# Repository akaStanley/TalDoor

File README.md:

# TalDoor (GatekeeperV2)
Spencer Kulbacki ~ CSH 2017-18

TalDoor (or GatekeeperV2) is a small POE door lock system that runs off the PocketBeagle and uses PN532 NFC module to scan and authenticate user ID cards and open the door.

## Hardware:
- [PocketBeagle](https://github.com/beagleboard/pocketbeagle)
- Pn532 NFC Module
- Esimated 500mA consumption of entire device during idle operation. Peak of 800mA during read/write  door motor operations. EST less than 3 WATT max POE requirements.

### Internal Main Board contains:
- PocketBeagle
- POE module
- Ethernet to SPI module
- Door lock motor driver
- 3.3 to 5v step up for motor drive
	
### External Reader Board contains:
- PN532 NFC reader
- Red/Green LEDs & Beeper for notification

### Part List for the PCB
+/- some pin headers we already have
~30$ in components for one board (+PCB Cost)

~62 components specified in BOM (not counting extra male pin headers)

QTY|Value
----|------
1|Buzzer
9|0.1uF
2|18pF
3|10uF
1|10000pF
1|10uF
1|470uF
3|1uF
4|G_LED
4|R_LED
1|SI-52003-F_RJ45
1|Conn_01x02
2|Conn_01x06_Male
1|Ferrite_Bead
1|PocketBeagle
1|RK7002BM
1|BSS223PWH6327XTSA1
1|100kΩ
2|10kΩ
2|180Ω
1|2.2kΩ
4|49.9Ω
8|68Ω
1|150Ω
1|DRV8837
1|ENC28J60-I/SO
1|PN532
1|AG9703
1|NCP1117-3.3
1|25MHz

## Software:
- LibNFC 1.7.1

## Notes
- [Paul's Github notes](https://github.com/woo2/gatekeeper-v2/tree/master/notes)
- [BestCo door lock info,sorta](http://www.bestaccess.com/files/6014/6184/1926/WMseries_WEB.pdf)
- Setting up ethernet forwarding over USB for BeagleBone dev on a PC
	- Plugin the BeagleBone to a USB port on your computer
	- Install the drivers
	- In control panel -> Adapter settings, set the IP address of the USB adapter to 192.168.7.1
	- On the adapter that has the internet connection, enable connection sharing with the USB adapter connection
	- ssh into the BeagleBone (ssh 192.168.7.2)
	- Run command "route add default gw 192.168.7.1"
	- Edit /etc/resolv.conf and add the Google name server by adding the line "nameserver 8.8.8.8"
	
- Door locks are 5v motors that need ~70mA to turn a worm gear and "unlock" the turnkey.
- BeagleBoard uses 130mA nom (300mA peak)
- 4 Red 0603 LEDs use 80mA
- ENC28J60-I/SO uses 120mA nom (180mA peak)
- PN532 91mA nom (140mA peak)
- Esimated 500mA consumption of entire device during idle operation. Peak of 800mA during read/write  door motor operations. EST less than 3 WATT max POE requirements.

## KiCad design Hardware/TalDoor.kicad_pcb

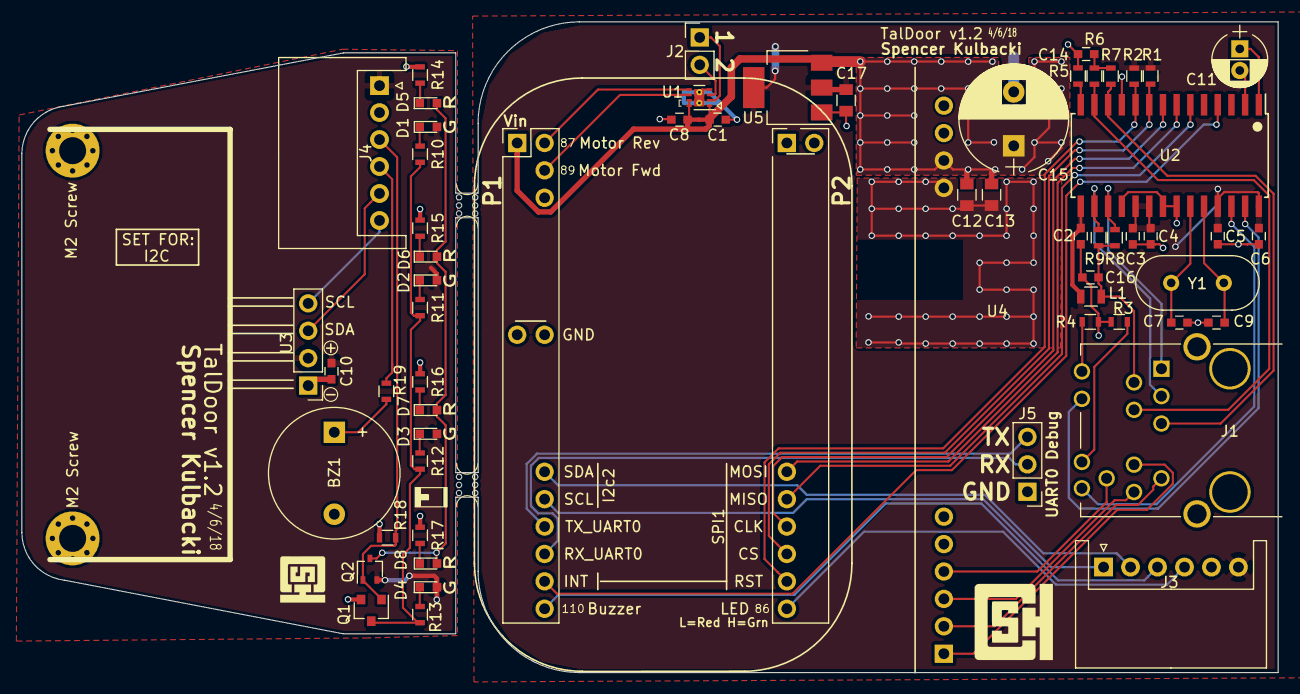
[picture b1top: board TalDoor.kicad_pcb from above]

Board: 2 copper layers, 116.5 x 60.3 mm, 64 parts (0 on the bottom side), 54 nets.

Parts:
BZ1: Buzzer; Buzzer_12x9.5RM7.6
C1, C2, C3, C4, C5, C6, C8, C10, C16: 0.1uF; C_0603
C7, C9: 18pF; C_0603
C11: 10uF; CP_Radial_D5.0mm_P2.00mm
C12, C13, C17: 10uF; C_0805
C14: 10000pF; C_0603
C15: 470uF; CP_Radial_D10.0mm_P5.00mm
D1, D2, D3, D4: G_LED; LED_0603
D5, D6, D7, D8: R_LED; LED_0603
J1: SI-52003-F_RJ45; RJ45_POE
J2: Conn_01x02; Pin_Header_Straight_1x02_Pitch2.54mm
J3, J4: Conn_01x06_Male; JST_XH_S06B-XH-A_06x2.50mm_Angled
J5: Conn_01x03; Pin_Header_Straight_1x03_Pitch2.54mm
L1: Ferrite_Bead; L_0805
M2 Screw, M2 Screw#2: MountingHole_2.2mm_M2_Pad_Via; MountingHole_2.5mm_Pad_Via
P1: PocketBeagle; PocketBeagle_TalDoor
Q1: RK7002BM; SOT-23
Q2: BSS223PWH6327XTSA1; SOT-323_SC-70
R1: 100k; R_0603
R2, R18: 10k; R_0603
R3, R4: 180; R_0603
R5: 2.2k; R_0603
R6, R7, R8, R9: 49.9; R_0603
R10, R11, R12, R13, R14, R15, R16, R17: 68; R_0603
R19: 120; R_0603
U1: DRV8837; WSON-8_1EP_2x2mm_Pitch0.5mm_ThermalVias
U2: ENC28J60-I/SO; SOIC-28W_7.5x17.9mm_Pitch1.27mm
U3: PN532
U4: AG9700; Ag9700_FP
U5: NCP1117-3.3_SOT223; SOT-223-3_TabPin2
Y1: 25MHz; Crystal_HC49-4H_Vertical
mouse-bite-2mm-slot, mouse-bite-2mm-slot#2: VAL**; mouse-bite-2mm-slot

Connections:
+3V3: C2.1, C3.1, C4.1, C5.1, C6.1, C17.1, J3.6, L1.2, R1.1, R2.1, U2.15, U2.19, U2.20, U2.25, U2.28, U5.2
+5V: C1.2, C8.2, C12.1, C13.1, C15.1, P1.1.1, U1.1, U1.7, U1.8, U4.8, U5.3
/+3.3v2: C10.2, D1.2, D2.2, D3.2, D4.2, J4.1, Q2.2, U3.2
/CLK: P1.2.29, U2.8
/CS: P1.2.31, R1.2, U2.9
/GND2: BZ1.2, C10.1, J4.2, Q1.2, R14.2, R15.2, R16.2, R17.2, R18.1, U3.1
/GPIO_86: J3.4, P1.2.35
/GPIO_87: P1.1.2, U1.5
/GPIO_89: P1.1.4, U1.6
/GPIO_110: J3.3, P1.1.36
/INT: P1.1.34, U2.4
/LEDA: J1.G+, U2.27
/LEDB: J1.Y+, U2.26
/MISO: P1.2.27, U2.6
/MOSI: P1.2.25, U2.7
/RST: P1.2.33, R2.2, U2.10
/RX_UART0: J5.2, P1.1.32
/SCL: J3.1, P1.1.28
/SDA: J3.2, P1.1.26
/TX_UART0: J5.3, P1.1.30
GND: C1.1, C2.2, C3.2, C4.2, C5.2, C6.2, C7.2, C8.1, C9.2, C11.2, C12.2, C13.2, C14.2, C15.2, C16.2, C17.2, J1.13, J3.5, J5.1, P1.1.15, P1.1.16, R3.1, R4.1, R5.1, U1.4, U2.2, U2.11, U2.18, U2.21, U2.22, U4.7, U5.1
unnamed: BZ1.1, R19.2
unnamed: C7.1, U2.23, Y1.2
unnamed: C9.1, U2.24, Y1.1
unnamed: C11.1, U2.1
unnamed: C14.1, R6.1, R7.1
unnamed: C16.1, J1.2, L1.1, R8.1, R9.1
unnamed: D1.1, R10.1
unnamed: D2.1, R11.1
unnamed: D3.1, R12.1
unnamed: D4.1, R13.1
unnamed: D5.1, R14.1
unnamed: D5.2, D6.2, D7.2, D8.2, Q2.3
unnamed: D6.1, R15.1
unnamed: D7.1, R16.1
unnamed: D8.1, R17.1
unnamed: J1.1, R8.2, U2.17
unnamed: J1.3, R9.2, U2.16
unnamed: J1.4, R6.2, U2.13
unnamed: J1.5, R7.2, U2.12
unnamed: J1.8, U4.1
unnamed: J1.9, U4.2
unnamed: J1.10, U4.3
unnamed: J1.11, U4.4
unnamed: J1.G-, R4.2
unnamed: J1.Y-, R3.2
unnamed: J2.1, U1.2
unnamed: J2.2, U1.3
unnamed: J4.3, Q1.1, Q2.1, R18.2
unnamed: J4.4, R19.1
unnamed: J4.5, U3.3
unnamed: J4.6, U3.4
unnamed: Q1.3, R10.2, R11.2, R12.2, R13.2
unnamed: R5.2, U2.14

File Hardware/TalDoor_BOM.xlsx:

TalDoor PCB
Generated: 4/8/2018 11:51:53 AM | 59
Component Count: | 59
Ref | QTY | Value | Footprint | Description | Digikey Part # | Per Unit | Cost | Notes
BZ1, | 1 | Buzzer | Buzzers_Beepers:Buzzer_12x9.5RM7.6 | Buzzer, polar | 668-1456-ND | 1.375 | 1.375
C2, C3, C4, C5, C6, C16, C1, C8, C10, | 9 | 0.1uF | Capacitors_SMD:C_0603 | Unpolarized capacitor | 478-10054-1-ND | 1.06E-2 | 9.5399999999999999E-2
C7, C9, | 2 | 18pF | Capacitors_SMD:C_0603 | Unpolarized capacitor | 1276-1089-1-ND | 1.1900000000000001E-2 | 2.3800000000000002E-2
C12, C13, C17 | 3 | 10uF | Capacitors_SMD:C_0805 | Unpolarized capacitor | 1276-1096-1-ND | 9.4E-2 | 0.28200000000000003
C14, | 1 | 10000pF | Capacitors_SMD:C_0603 | Unpolarized capacitor | 1276-1132-1-ND | 7.4999999999999997E-3 | 7.4999999999999997E-3
C11, | 1 | 10uF | Capacitors_THT:CP_Radial_D5.0mm_P2.00mm | Polarised capacitor | 399-6597-ND | 0.105 | 0.105
C15, | 1 | 470uF | Capacitors_THT:CP_Radial_D10.0mm_P5.00mm | Polarised capacitor | 493-11709-1-ND | 0.311 | 0.311 | OLD taller one: 493-5907-1-ND
D2, D1, D3, D4, | 4 | G_LED | LEDs:LED_0603 | Green LED | VLMG1300-GS08CT-ND | 0.33700000000000002 | 1.3480000000000001
D5, D6, D7, D8, | 4 | R_LED | LEDs:LED_0603 | Super Red LED | VLMS1300-GS08CT-ND | 0.317 | 1.268
J1, | 1 | SI-52003-F_RJ45 | TalDoor_Footprints:RJ45_POE | TH RJ45 with transformer + leds | 380-1119-ND | 5.1100000000000003 | 5.1100000000000003 | No EMI Fingers, but different pinout: ARJ11D-MDSD-A-B-FLT2-ND
J2, | 1 | Conn_01x02 | Pin_Headers:Pin_Header_Straight_1x02_Pitch2.54mm | Generic connector, single row, 01x02 |  |  | 0
J4, J3, | 2 | Conn_01x06_Male | Connectors_JST:JST_XH_S06B-XH-A_06x2.50mm_Angled | Generic connector, single row, 01x06 | 455-2236-ND | 0.36799999999999999 | 0.73599999999999999 | Cables: https://www.amazon.com/uxcell-2-54mm-JST-XH-Adapter-Extensio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
L1, | 1 | Ferrite_Bead | Inductors_SMD:L_0805 | Ferrite bead | 490-7821-1-ND | 0.14099999999999999 | 0.14099999999999999
P1 | 1 | PocketBeagle | TalDoor_Footprints:PocketBeagle_TalDoor | double row, odd1/even2 numbering |  |  | 0 | Bespoke Female/Male Pin Headers (SIP sockets?)
Q1, | 1 | RK7002BM | TO_SOT_Packages_SMD:SOT-23 | Transistor N-MOSFET (general) | RK7002BMT116CT-ND | 0.16 | 0.16 | Nmos
Q2, | 1 | BSS223PWH6327XTSA1 | TO_SOT_Packages_SMD:SOT-323_SC-70 | P-MOSFET with substrate diode BSS223PWH6327XTSA1 | BSS223PWH6327XTSA1CT-ND | 0.30299999999999999 | 0.30299999999999999 | Pmos
R1, | 1 | 100kΩ | Resistors_SMD:R_0603 | Resistor | CR0603-JW-104ELFCT-ND | 8.0000000000000002E-3 | 8.0000000000000002E-3
R2, R18, | 2 | 10kΩ | Resistors_SMD:R_0603 | Resistor | CR0603-JW-103ELFCT-ND | 1.6E-2 | 3.2000000000000001E-2
R3, R4, | 2 | 180Ω | Resistors_SMD:R_0603 | Resistor | RMCF0603JT180RCT-ND | 1.2999999999999999E-2 | 2.5999999999999999E-2
R5, | 1 | 2.2kΩ | Resistors_SMD:R_0603 | Resistor | CR0603-JW-222ELFCT-ND | 1.6E-2 | 1.6E-2
R9, R8, R7, R6, | 4 | 49.9Ω | Resistors_SMD:R_0603 | Resistor | CR0603-FX-49R9ELFCT-ND | 9.9000000000000008E-3 | 3.9600000000000003E-2
R14, R10, R11, R12, R15, R16, R13, R17, | 8 | 68Ω | Resistors_SMD:R_0603 | Resistor | CR0603-JW-680ELFCT-ND | 1.6E-2 | 0.128
R19, | 1 | 120Ω | Resistors_SMD:R_0603 | Resistor | CR0603-JW-121ELFCT-ND | 1.6E-2 | 1.6E-2
U1, | 1 | DRV8837 | Housings_SON:WSON-8_1EP_2x2mm_Pitch0.5mm_ThermalVias | IC MOTOR DRIVER, 2 Half bridges | 296-34806-1-ND | 1.2310000000000001 | 1.2310000000000001
U2, | 1 | ENC28J60-I/SO | Housings_SOIC:SOIC-28W_7.5x17.9mm_Pitch1.27mm | ENC28J60 Single Chip Ethernet Interface, SOIC-28 | ENC28J60-I/SO-ND | 2.7559999999999998 | 2.7559999999999998
U3, | 1 | PN532 | Pin_Headers:Pin_Header_Straight_1x04_Pitch2.54mm | Pn532 NFC reader over I2C |  | 6.63 | 6.63 | PN532
U4, | 1 | AG9705 | TalDoor_Footprints:Ag9700_FP | 48v POE stepdown transformer and voltage supply |  | 7.29 | 7.29 | Ag9705-2BR
U5, | 1 | NCP1117-3.3_SOT223 | TO_SOT_Packages_SMD:SOT-223-3_TabPin2 | 1A Low Dropout regulator, positive, 1.5V fixed output, SOT-223 | 497-1228-1-ND | 0.60299999999999998 | 0.60299999999999998
Y1, | 1 | 25MHz | Crystals:Crystal_HC49-4H_Vertical | Two pin crystal | 631-1112-ND | 0.32 | 0.32
 |  |  |  |  |  | 30.3613

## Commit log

2017-10-28 added datasheets
2017-10-28 Datasheets and readme block diagram
2017-10-30 added more notes
2017-10-31 added LED links
2017-10-31 added buzzer
2017-11-03 EOL part number substitute
2017-11-03 I cant make lists correctly whoops
2017-12-28 Started KiCad Schematic. Added project specific parts library. linked some datasheets
2017-12-29 Added parts for Ethernet jack and PocketBeagle IO
2017-12-29 Added all parts but motor drive. updated readme parts list
2017-12-29 added motor driver
2017-12-29 cleaned up some of schematic
2017-12-31 Added footprints to all parts
2018-01-02 generated BOM with pricing
2018-01-02 started PCB, added 3d models for all parts
2018-01-03 Added connectors, moved notifications to external PCB
2018-01-03 added datasheet
2018-01-04 Solution to 1 wire LED nitification issue. See LED_NotificationModel.txt
2018-01-04 Updated schematic with N/Pmos LED format for single IO drive. Updated BOM
2018-01-05 Secondary PCB layout complete
2018-01-05 adding measurements for main PCB
2018-01-06 Completed Mainboard PCB, needs Vgroove/Mousebite connection between two. Also check motor driver
2018-01-06 Added PCB Photos and Schematic PDFs for info
2018-01-06 URLs get me every time.
2018-01-06 Added 5v motor control. Updated schematic, images, BOM, PCB layout
2018-01-06 updated PCB
2018-01-08 updated bom
2018-01-29 Started changed base on Hardware 1 build
2018-01-29 generated new bom file, need to be combined and updated with old one.
2018-02-03 Updating PCB layout, unfinished
2018-02-03 fixed fills so there is no DRC error
2018-02-12 Updated PCB layout for fixes from v1
2018-02-16 Updated PCB with solder jumpers for easier developing
2018-02-16 Updated board photos and readme
2018-02-17 ordered V1.1 boards
2018-02-17 updated part number
2018-02-24 Updated Drawings and schematic pdfs
2018-03-09 updated schematic rev & date, bom
2018-03-10 updated layout to account for door mount shape issue
2018-04-07 fixed ethernet module, SPI, I2c busses
2018-04-08 Updated PCB and added new photos
2018-04-08 updated main project file date
2018-04-24 updated schematic
